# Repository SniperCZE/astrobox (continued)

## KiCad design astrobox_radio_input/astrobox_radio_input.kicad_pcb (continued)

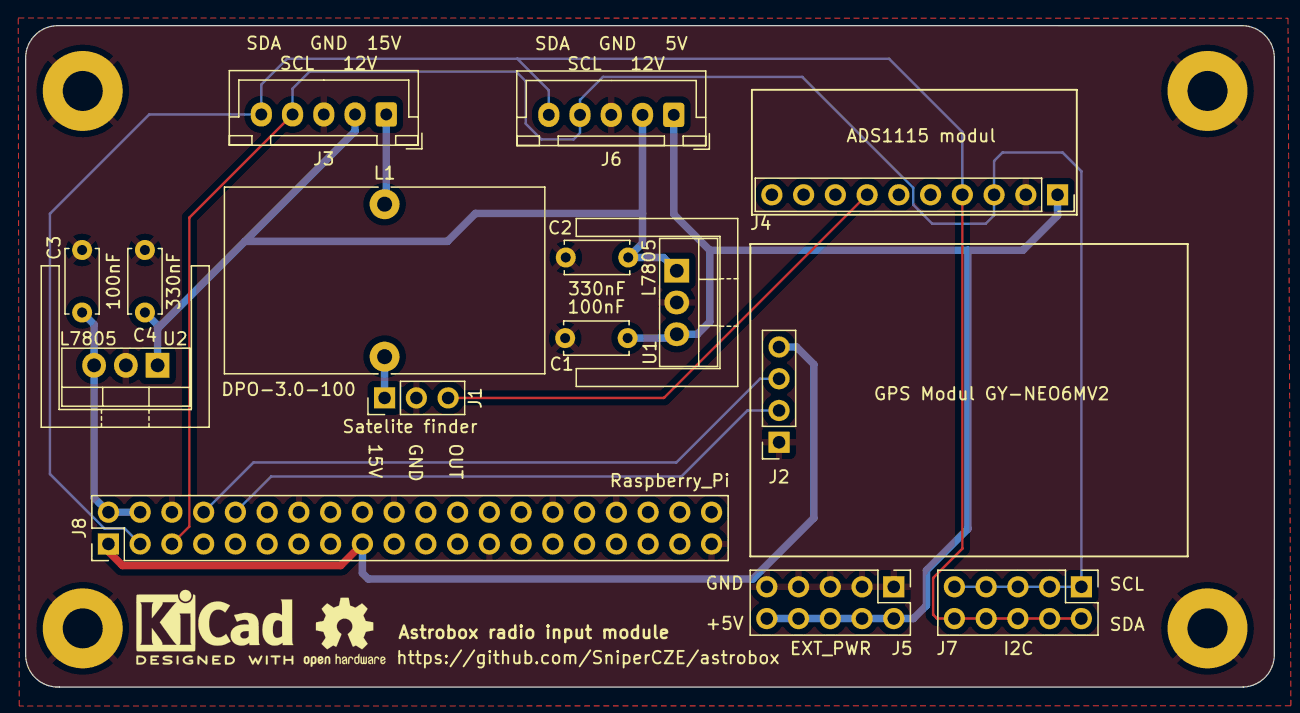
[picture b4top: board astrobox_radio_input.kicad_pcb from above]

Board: 2 copper layers, 99.9 x 52.9 mm, 15 parts (0 on the bottom side), 12 nets.

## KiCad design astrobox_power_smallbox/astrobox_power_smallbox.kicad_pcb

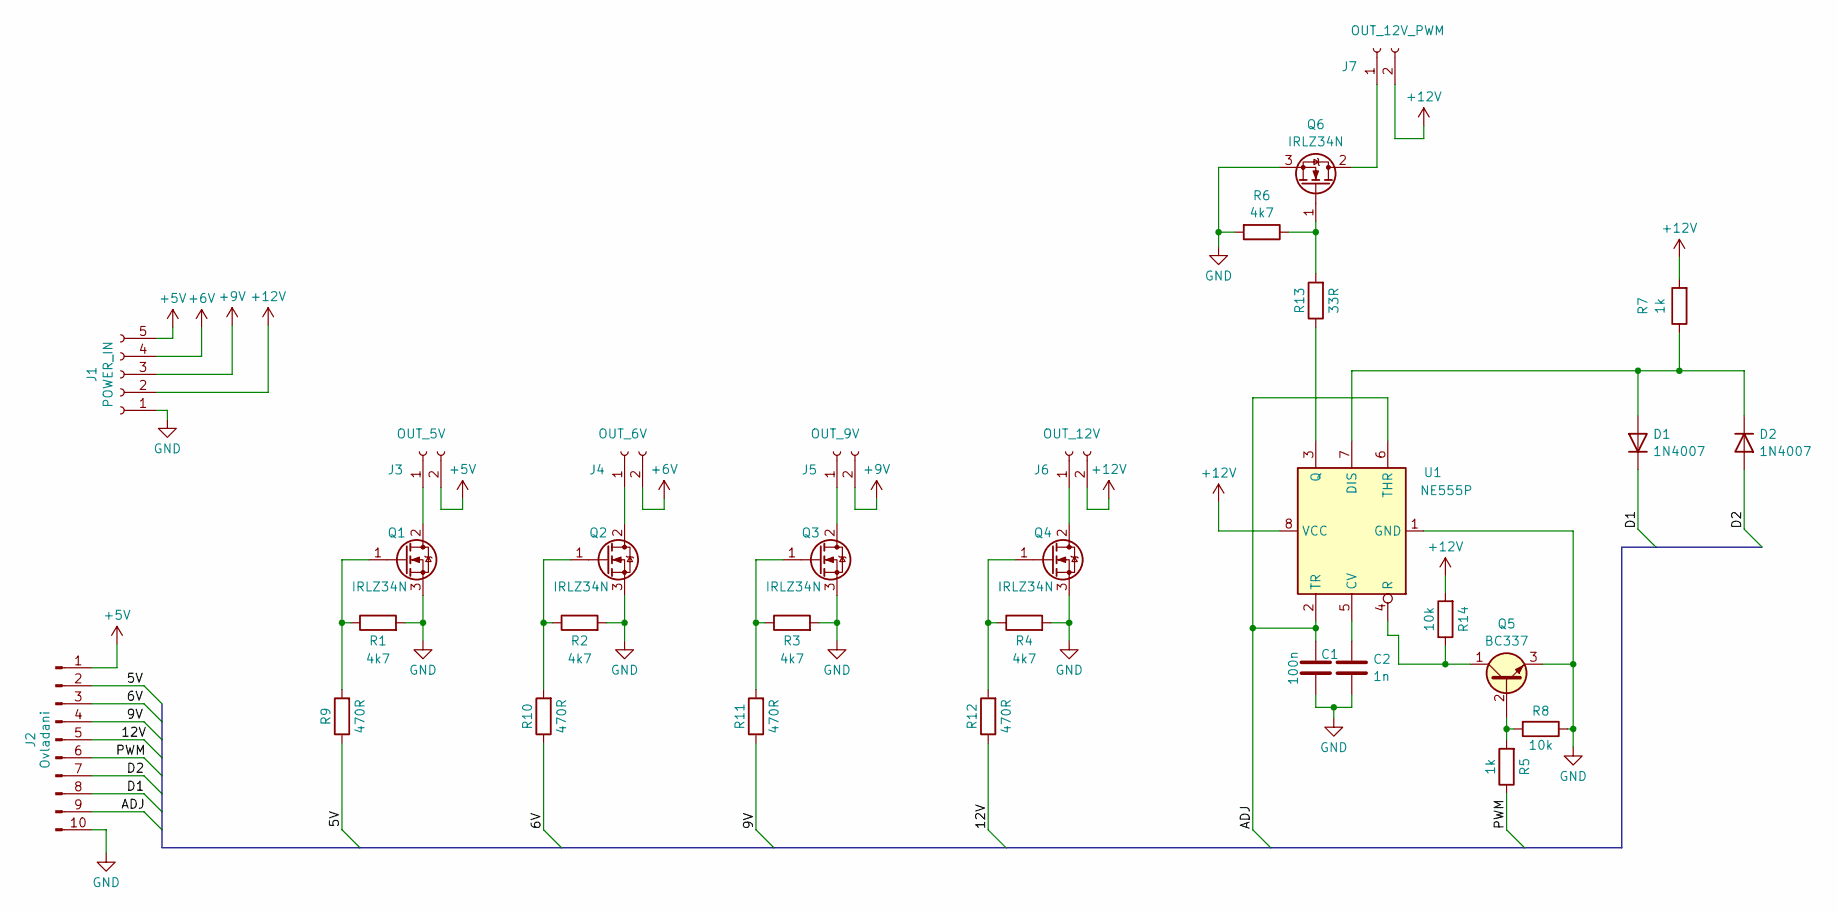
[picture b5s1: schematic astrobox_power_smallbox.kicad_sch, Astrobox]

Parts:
C1: 100n; C_Disc_D9.0mm_W5.0mm_P5.00mm
C2: 1n; C_Disc_D9.0mm_W5.0mm_P5.00mm
D1, D2: 1N4007; D_DO-15_P12.70mm_Horizontal
J1: POWER_IN; SolderWire-1sqmm_1x05_P5.4mm_D1.4mm_OD2.7mm
J2: Ovladani; PinHeader_1x10_P2.54mm_Vertical
J3: OUT_5V; SolderWire-1.5sqmm_1x02_P6mm_D1.7mm_OD3mm
J4: OUT_6V; SolderWire-1.5sqmm_1x02_P6mm_D1.7mm_OD3mm
J5: OUT_9V; SolderWire-1.5sqmm_1x02_P6mm_D1.7mm_OD3mm
J6: OUT_12V; SolderWire-1.5sqmm_1x02_P6mm_D1.7mm_OD3mm
J7: OUT_12V_PWM; SolderWire-1.5sqmm_1x02_P6mm_D1.7mm_OD3mm
Q1, Q2, Q3, Q4, Q6: IRLZ34N; TO-220-3_Vertical
Q5: BC337; TO-92_HandSolder
R1, R2, R3, R4, R6: 4k7; R_Axial_DIN0309_L9.0mm_D3.2mm_P12.70mm_Horizontal
R5, R7: 1k; R_Axial_DIN0309_L9.0mm_D3.2mm_P12.70mm_Horizontal
R8, R14: 10k; R_Axial_DIN0309_L9.0mm_D3.2mm_P12.70mm_Horizontal
R9, R10, R11, R12: 470R; R_Axial_DIN0309_L9.0mm_D3.2mm_P12.70mm_Horizontal
R13: 33R; R_Axial_DIN0309_L9.0mm_D3.2mm_P12.70mm_Horizontal
U1: NE555P; DIP-8_W7.62mm

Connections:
+5V: J1.5, J2.1, J3.2
+6V: J1.4, J4.2
+9V: J1.3, J5.2
+12V: J1.2, J6.2, J7.2, R7.2, R14.2, U1.8 (VCC)
/5V: J2.2, R9.1
/6V: J2.3, R10.1
/9V: J2.4, R11.1
/12V: J2.5, R12.1
/ADJ: C1.1, J2.9, U1.2 (TR), U1.6 (THR)
/D1: D1.1 (K), J2.8
/D2: D2.2 (A), J2.7
/PWM: J2.6, R5.1
GND: C1.2, C2.2, J1.1, J2.10, Q1.3 (S), Q2.3 (S), Q3.3 (S), Q4.3 (S), Q5.3 (E), Q6.3 (S), R1.2, R2.2, R3.2, R4.2, R6.2, R8.1, U1.1 (GND)
unnamed: D1.2 (A), D2.1 (K), R7.1, U1.7 (DIS)
unnamed: J3.1, Q1.2 (D)
unnamed: J4.1, Q2.2 (D)
unnamed: J5.1, Q3.2 (D)
unnamed: J6.1, Q4.2 (D)
unnamed: J7.1, Q6.2 (D)
unnamed: Q1.1 (G), R1.1, R9.2
unnamed: Q2.1 (G), R2.1, R10.2
unnamed: Q3.1 (G), R3.1, R11.2
unnamed: Q4.1 (G), R4.1, R12.2
unnamed: Q5.2 (B), R5.2, R8.2
unnamed: Q5.1 (C), R14.1, U1.4 (R)
unnamed: Q6.1 (G), R6.1, R13.2
unnamed: C2.1, U1.5 (CV)
unnamed: R13.1, U1.3 (Q)

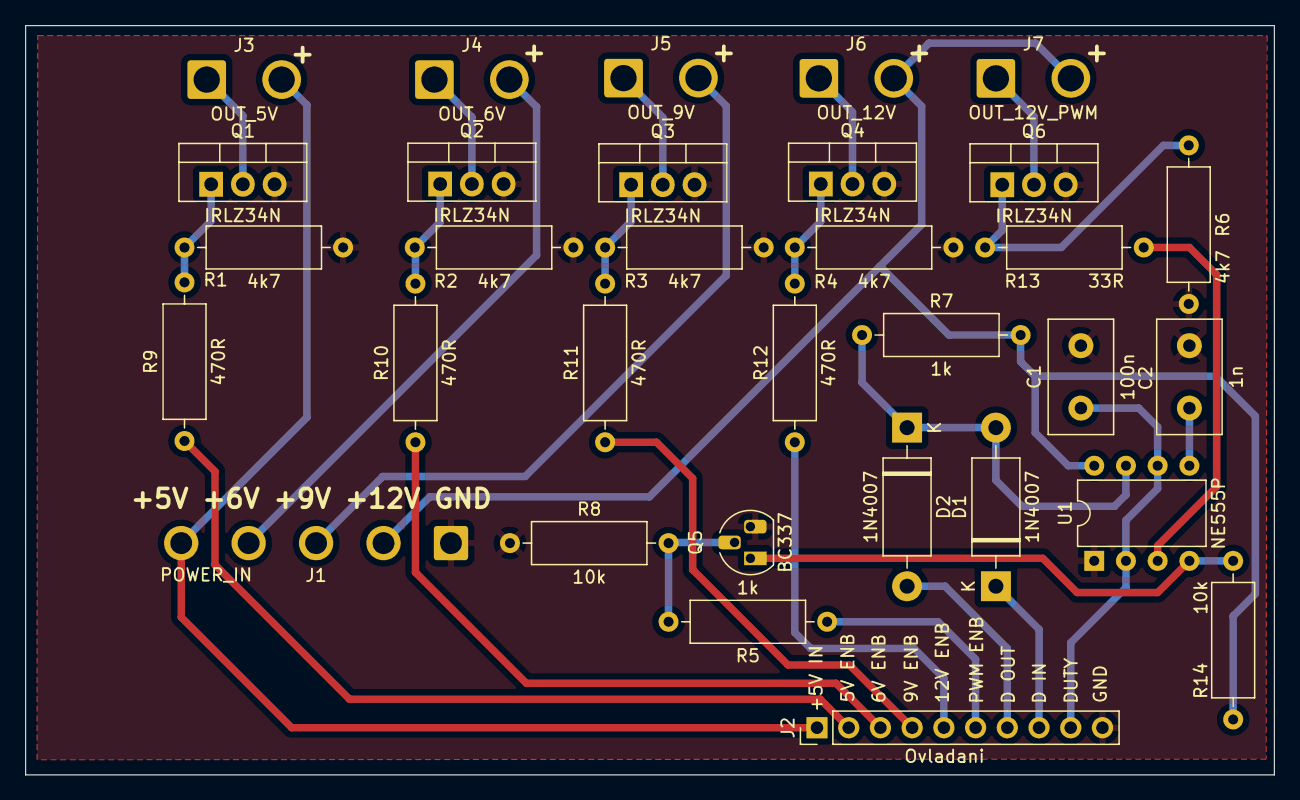
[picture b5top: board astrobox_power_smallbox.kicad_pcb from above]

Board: 2 copper layers, 100.0 x 60.0 mm, 32 parts (0 on the bottom side), 28 nets.

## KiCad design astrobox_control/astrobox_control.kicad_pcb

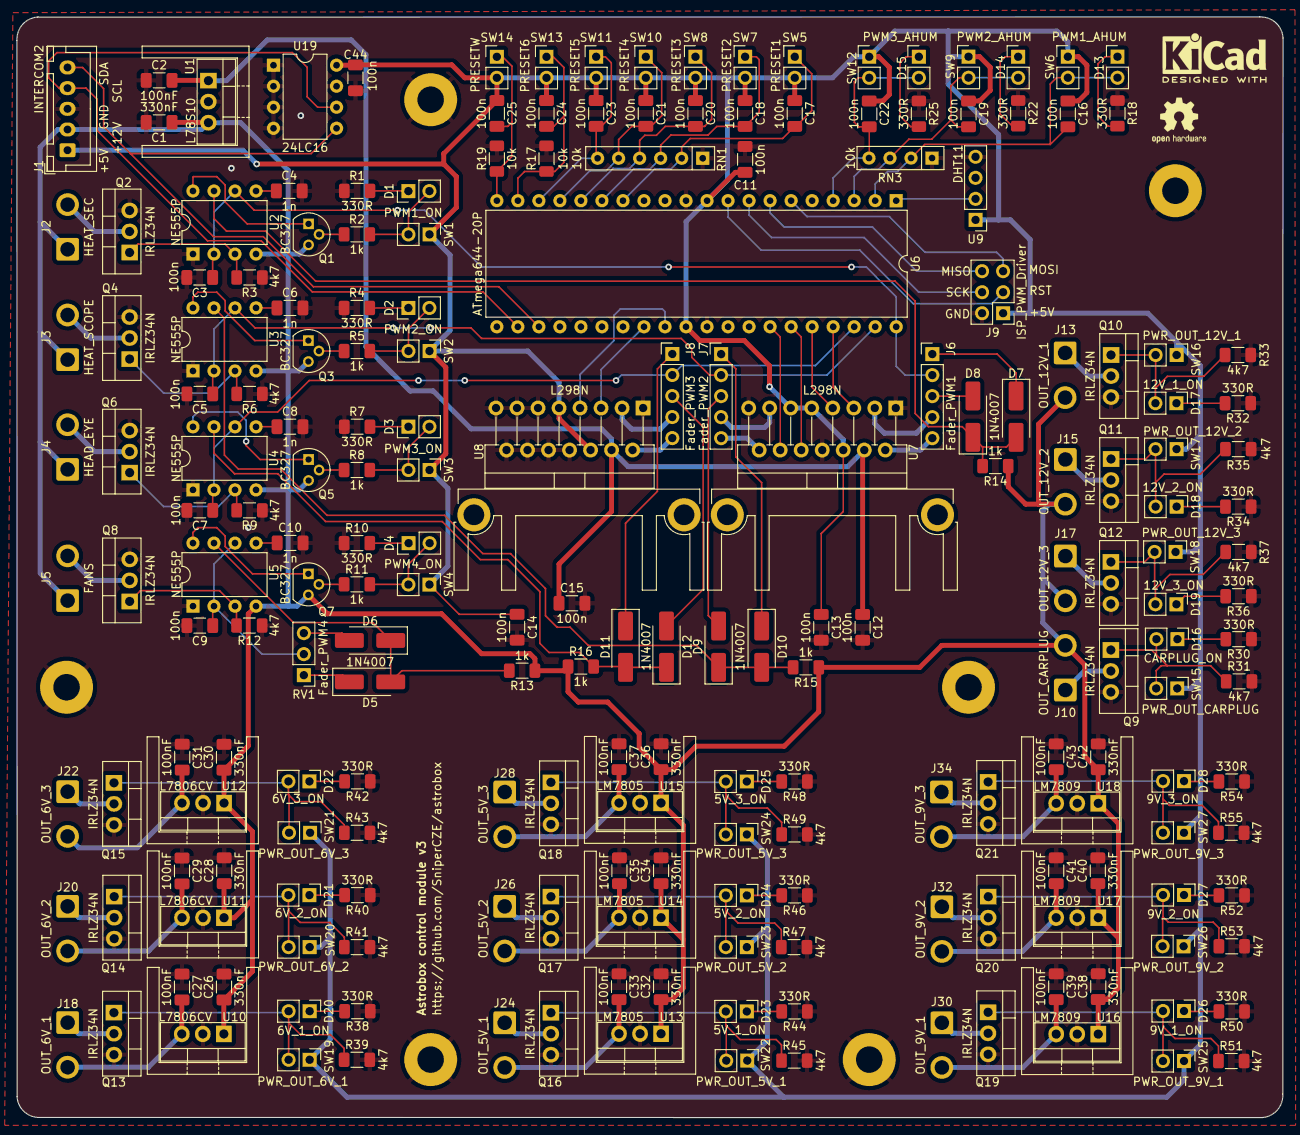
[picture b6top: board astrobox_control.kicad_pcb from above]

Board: 2 copper layers, 153.0 x 133.0 mm, 211 parts (0 on the bottom side), 128 nets.

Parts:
C1, C26, C28, C30, C32, C34, C36, C38, C40, C42: 330nF; C_1206_3216Metric_Pad1.33x1.80mm_HandSolder
C2, C27, C29, C31, C33, C35, C37, C39, C41, C43: 100nF; C_1206_3216Metric_Pad1.33x1.80mm_HandSolder
C3, C5, C7, C9, C11, C12, C13, C14, C15, C16, C17, C18, C19, C20, C21, C22, C23, C24, C25, C44: 100n; C_1206_3216Metric_Pad1.33x1.80mm_HandSolder
C4, C6, C8, C10: 1n; C_1206_3216Metric_Pad1.33x1.80mm_HandSolder
D1: PWM1_ON; PinHeader_1x02_P2.54mm_Vertical
D2: PWM2_ON; PinHeader_1x02_P2.54mm_Vertical
D3: PWM3_ON; PinHeader_1x02_P2.54mm_Vertical
D4: PWM4_ON; PinHeader_1x02_P2.54mm_Vertical
D5, D6, D7, D8, D9, D10, D11, D12: 1N4007; D_SMA_Handsoldering
D13: PWM1_AHUM; PinHeader_1x02_P2.54mm_Vertical
D14: PWM2_AHUM; PinHeader_1x02_P2.54mm_Vertical
D15: PWM3_AHUM; PinHeader_1x02_P2.54mm_Vertical
D16: CARPLUG_ON; PinHeader_1x02_P2.54mm_Vertical
D17: 12V_1_ON; PinHeader_1x02_P2.54mm_Vertical
D18: 12V_2_ON; PinHeader_1x02_P2.54mm_Vertical
D19: 12V_3_ON; PinHeader_1x02_P2.54mm_Vertical
D20: 6V_1_ON; PinHeader_1x02_P2.54mm_Vertical
D21: 6V_2_ON; PinHeader_1x02_P2.54mm_Vertical
D22: 6V_3_ON; PinHeader_1x02_P2.54mm_Vertical
D23: 5V_1_ON; PinHeader_1x02_P2.54mm_Vertical
D24: 5V_2_ON; PinHeader_1x02_P2.54mm_Vertical
D25: 5V_3_ON; PinHeader_1x02_P2.54mm_Vertical
D26: 9V_1_ON; PinHeader_1x02_P2.54mm_Vertical
D27: 9V_2_ON; PinHeader_1x02_P2.54mm_Vertical
D28: 9V_3_ON; PinHeader_1x02_P2.54mm_Vertical
J1: INTERCOM2; JST_XH_B5B-XH-A_1x05_P2.50mm_Vertical
J2: HEAT_SEC; SolderWire-1sqmm_1x02_P5.4mm_D1.4mm_OD2.7mm
J3: HEAT_SCOPE; SolderWire-1sqmm_1x02_P5.4mm_D1.4mm_OD2.7mm
J4: HEAD_EYE; SolderWire-1sqmm_1x02_P5.4mm_D1.4mm_OD2.7mm
J5: FANS; SolderWire-1sqmm_1x02_P5.4mm_D1.4mm_OD2.7mm
J6: Fader_PWM1; PinHeader_1x05_P2.54mm_Vertical
J7: Fader_PWM2; PinHeader_1x05_P2.54mm_Vertical
J8: Fader_PWM3; PinHeader_1x05_P2.54mm_Vertical
J9: ISP_PWM_Driver; PinHeader_2x03_P2.54mm_Vertical
J10: OUT_CARPLUG; SolderWire-1sqmm_1x02_P5.4mm_D1.4mm_OD2.7mm
J13: OUT_12V_1; SolderWire-1sqmm_1x02_P5.4mm_D1.4mm_OD2.7mm
J15: OUT_12V_2; SolderWire-1sqmm_1x02_P5.4mm_D1.4mm_OD2.7mm
J17: OUT_12V_3; SolderWire-1sqmm_1x02_P5.4mm_D1.4mm_OD2.7mm
J18: OUT_6V_1; SolderWire-1sqmm_1x02_P5.4mm_D1.4mm_OD2.7mm
J20: OUT_6V_2; SolderWire-1sqmm_1x02_P5.4mm_D1.4mm_OD2.7mm
J22: OUT_6V_3; SolderWire-1sqmm_1x02_P5.4mm_D1.4mm_OD2.7mm
J24: OUT_5V_1; SolderWire-1sqmm_1x02_P5.4mm_D1.4mm_OD2.7mm
J26: OUT_5V_2; SolderWire-1sqmm_1x02_P5.4mm_D1.4mm_OD2.7mm
J28: OUT_5V_3; SolderWire-1sqmm_1x02_P5.4mm_D1.4mm_OD2.7mm
J30: OUT_9V_1; SolderWire-1sqmm_1x02_P5.4mm_D1.4mm_OD2.7mm
J32: OUT_9V_2; SolderWire-1sqmm_1x02_P5.4mm_D1.4mm_OD2.7mm
J34: OUT_9V_3; SolderWire-1sqmm_1x02_P5.4mm_D1.4mm_OD2.7mm
Q1, Q3, Q5, Q7: BC327; TO-92
Q2, Q4, Q6, Q8, Q9, Q10, Q11, Q12, Q13, Q14, Q15, Q16, Q17, Q18, Q19, Q20, Q21: IRLZ34N; TO-220-3_Vertical
R1, R4, R7, R10, R18, R22, R25, R30, R32, R34, R36, R38, R40, R42, R44, R46, R48, R50, R52, R54: 330R; R_1206_3216Metric_Pad1.30x1.75mm_HandSolder
R2, R5, R8, R11, R13, R14, R15, R16: 1k; R_1206_3216Metric_Pad1.30x1.75mm_HandSolder
R3, R6, R9, R12, R31, R33, R35, R37, R39, R41, R43, R45, R47, R49, R51, R53, R55: 4k7; R_1206_3216Metric_Pad1.30x1.75mm_HandSolder
R17, R19: 10k; R_1206_3216Metric_Pad1.30x1.75mm_HandSolder
RN1: 10k; R_Array_SIP6
RN3: 10k; R_Array_SIP4
RV1: Fader_PWM4; PinHeader_1x03_P2.54mm_Vertical
SW1: PWM1_ON; PinHeader_1x02_P2.54mm_Vertical
SW2: PWM2_ON; PinHeader_1x02_P2.54mm_Vertical
SW3: PWM3_ON; PinHeader_1x02_P2.54mm_Vertical
SW4: PWM4_ON; PinHeader_1x02_P2.54mm_Vertical
SW5: PRESET1; PinHeader_1x02_P2.54mm_Vertical
SW6: PWM1_AUTOHUM; PinHeader_1x02_P2.54mm_Vertical
SW7: PRESET2; PinHeader_1x02_P2.54mm_Vertical
SW8: PRESET3; PinHeader_1x02_P2.54mm_Vertical
SW9: PWM2_AUTOHUM; PinHeader_1x02_P2.54mm_Vertical
SW10: PRESET4; PinHeader_1x02_P2.54mm_Vertical
SW11: PRESET5; PinHeader_1x02_P2.54mm_Vertical
SW12: PWM3_AUTOHUM; PinHeader_1x02_P2.54mm_Vertical
SW13: PRESET6; PinHeader_1x02_P2.54mm_Vertical
SW14: PRESETW; PinHeader_1x02_P2.54mm_Vertical
SW15: PWR_OUT_CARPLUG; PinHeader_1x02_P2.54mm_Vertical
SW16: PWR_OUT_12V_1; PinHeader_1x02_P2.54mm_Vertical
SW17: PWR_OUT_12V_2; PinHeader_1x02_P2.54mm_Vertical
SW18: PWR_OUT_12V_3; PinHeader_1x02_P2.54mm_Vertical
SW19: PWR_OUT_6V_1; PinHeader_1x02_P2.54mm_Vertical
SW20: PWR_OUT_6V_2; PinHeader_1x02_P2.54mm_Vertical
SW21: PWR_OUT_6V_3; PinHeader_1x02_P2.54mm_Vertical
SW22: PWR_OUT_5V_1; PinHeader_1x02_P2.54mm_Vertical
SW23: PWR_OUT_5V_2; PinHeader_1x02_P2.54mm_Vertical
SW24: PWR_OUT_5V_3; PinHeader_1x02_P2.54mm_Vertical
SW25: PWR_OUT_9V_1; PinHeader_1x02_P2.54mm_Vertical
SW26: PWR_OUT_9V_2; PinHeader_1x02_P2.54mm_Vertical
SW27: PWR_OUT_9V_3; PinHeader_1x02_P2.54mm_Vertical
U1: L78S10; TO-220-3_Vertical
U2, U3, U4, U5: NE555P; DIP-8_W7.62mm
U6: ATmega644-20P; DIP-40_W15.24mm
U7, U8: L298N; TO-220-15_P2.54x2.54mm_StaggerOdd_Lead4.58mm_Vertical
U9: DHT11; PinHeader_1x04_P2.54mm_Vertical
U10, U11, U12: L7806CV; TO-220-3_Vertical
U13, U14, U15: LM7805; TO-220-3_Vertical
U16, U17, U18: LM7809; TO-220-3_Vertical
U19: 24LC16; DIP-8_W7.62mm

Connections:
+5V: C11.1, C13.1, C14.1, C16.1, C17.1, C18.1, C19.1, C20.1, C21.1, C22.1, C23.1, C24.1, C25.1, C44.1, J1.1, J9.1, SW1.1 (A), SW2.1 (A), SW3.1 (A), SW4.1 (A), SW5.2, SW6.1 (A), SW7.2, SW8.2, SW9.1 (A), SW10.2, SW11.2, SW12.1 (A), SW13.2, SW14.2, SW15.1 (A), SW16.1 (A), SW17.1 (A), SW18.1 (A), SW19.1 (A), SW20.1 (A), SW21.1 (A), SW22.1 (A), SW23.1 (A), SW24.1 (A), SW25.1 (A), SW26.1 (A), SW27.1 (A), U6.10 (VCC), U6.30 (AVCC), U7.6 (EnA), U7.9 (Vss), U7.11 (EnB), U8.6 (EnA), U8.9 (Vss), U9.1 (VDD), U19.8 (VCC)
+10V: C2.2, C12.1, C15.1, U1.1 (VO), U7.4 (Vs), U8.4 (Vs)
+12V: C1.1, C26.1, C28.1, C30.1, C32.1, C34.1, C36.1, C38.1, C40.1, C42.1, J1.2, J2.1, J3.1, J4.1, J5.1, J10.2, J13.2, J15.2, J17.2, Q1.3 (E), Q3.3 (E), Q5.3 (E), Q7.3 (E), R13.1, R14.1, R15.1, R16.1, U1.3 (VI), U2.4 (R), U3.4 (R), U4.4 (R), U5.4 (R), U10.1 (VI), U11.1 (VI), U12.1 (VI), U13.1 (VI), U14.1 (VI), U15.1 (VI), U16.1 (VI), U17.1 (VI), U18.1 (VI)
/PWM control plane/AUTOHUM1: C16.2, D13.2 (A), RN3.2 (R1.2), SW6.2 (B), U6.2 (PB1)
/PWM control plane/AUTOHUM2: C19.2, D14.2 (A), RN3.3 (R2.2), SW9.2 (B), U6.3 (PB2)
/PWM control plane/AUTOHUM3: C22.2, D15.2 (A), RN3.4 (R3.2), SW12.2 (B), U6.4 (PB3)
/PWM control plane/DHT11: U6.1 (PB0), U9.2 (DATA)
/PWM control plane/FADER1: C3.1, J6.2, U2.2 (TR), U2.6 (THR), U6.40 (PA0)
/PWM control plane/FADER2: C5.1, J7.2, U3.2 (TR), U3.6 (THR), U6.39 (PA1)
/PWM control plane/FADER3: C7.1, J8.2, U4.2 (TR), U4.6 (THR), U6.38 (PA2)
/PWM control plane/MISO: J9.6, U6.7 (PB6)
/PWM control plane/MOSI: J9.5, U6.6 (PB5)
/PWM control plane/PRESET1: C17.2, RN1.2 (R1.2), SW5.1, U6.14 (PD0)
/PWM control plane/PRESET2: C18.2, RN1.3 (R2.2), SW7.1, U6.15 (PD1)
/PWM control plane/PRESET3: C20.2, RN1.4 (R3.2), SW8.1, U6.16 (PD2)
/PWM control plane/PRESET4: C21.2, RN1.5 (R4.2), SW10.1, U6.17 (PD3)
/PWM control plane/PRESET5: C23.2, RN1.6 (R5.2), SW11.1, U6.18 (PD4)
/PWM control plane/PRESET6: C24.2, R17.1, SW13.1, U6.19 (PD5)
/PWM control plane/PRESETW: C25.2, R19.1, SW14.1, U6.20 (PD6)
/PWM control plane/PWM_1 555-7 OUT: D7.2 (A), D8.1 (K), R14.2, U2.7 (DIS)
/PWM control plane/PWM_2 555-7 OUT: D9.1 (K), D10.2 (A), R15.2, U3.7 (DIS)
/PWM control plane/PWM_3 555-7 OUT: D11.2 (A), D12.1 (K), R16.2, U4.7 (DIS)
/PWM control plane/PWM_4 555-7 OUT: D5.2 (A), D6.1 (K), R13.2, U5.7 (DIS)
/PWM control plane/PWM_4 OUT: C9.1, RV1.2, U5.2 (TR), U5.6 (THR)
/PWM control plane/RST: J9.3, U6.9 (~RESET)
/PWM control plane/SCK: J9.4, U6.8 (PB7)
/PWM control plane/SCL: J1.4, U6.22 (PC0), U19.6 (SCL)
/PWM control plane/SDA: J1.5, U6.23 (PC1), U19.5 (SDA)
GND: C1.2, C2.1, C3.2, C4.2, C5.2, C6.2, C7.2, C8.2, C9.2, C10.2, C11.2, C12.2, C13.2, C14.2, C15.2, C26.2, C27.1, C28.2, C29.1, C30.2, C31.1, C32.2, C33.1, C34.2, C35.1, C36.2, C37.1, C38.2, C39.1, C40.2, C41.1, C42.2, C43.1, C44.2, J1.3, J9.2, Q2.3 (S), Q4.3 (S), Q6.3 (S), Q8.3 (S), Q9.3 (S), Q10.3 (S), Q11.3 (S), Q12.3 (S), Q13.3 (S), Q14.3 (S), Q15.3 (S), Q16.3 (S), Q17.3 (S), Q18.3 (S), Q19.3 (S), Q20.3 (S), Q21.3 (S), R1.1, R3.1, R4.1, R6.1, R7.1, R9.1, R10.1, R12.1, R17.2, R18.1, R19.2, R22.1, R25.1, R30.1, R31.2, R32.1, R33.2, R34.1, R35.2, R36.1, R37.2, R38.1, R39.2, R40.1, R41.2, R42.1, R43.2, R44.1, R45.2, R46.1, R47.2, R48.1, R49.2, R50.1, R51.2, R52.1, R53.2, R54.1, R55.2, RN1.1 (R1), RN3.1 (R1), U1.2 (GND), U2.1 (GND), U3.1 (GND), U4.1 (GND), U5.1 (GND), U6.11 (GND), U6.31 (GND), U7.1 (SENSE_A), U7.8 (GND), U7.15 (SENSE_B), U8.1 (SENSE_A), U8.8 (GND), U8.10 (IN3), U8.11 (EnB), U8.12 (IN4), U8.13 (OUT3), U8.14 (OUT4), U8.15 (SENSE_B), U9.4 (GND), U10.2 (GND), U11.2 (GND), U12.2 (GND), U13.2 (GND), U14.2 (GND), U15.2 (GND), U16.2 (GND), U17.2 (GND), U18.2 (GND), U19.1 (A0), U19.2 (A1), U19.3 (A2), U19.4 (GND), U19.7 (WP)
unnamed: D1.2 (A), R2.2, SW1.2 (B)
unnamed: D1.1 (K), R1.2
unnamed: D2.2 (A), R5.2, SW2.2 (B)
unnamed: D2.1 (K), R4.2
unnamed: D3.2 (A), R8.2, SW3.2 (B)
unnamed: D3.1 (K), R7.2
unnamed: D4.2 (A), R11.2, SW4.2 (B)
unnamed: D4.1 (K), R10.2
unnamed: D5.1 (K), RV1.1
unnamed: D6.2 (A), RV1.3
unnamed: D7.1 (K), J6.1
unnamed: D8.2 (A), J6.3
unnamed: D9.2 (A), J7.3
unnamed: D10.1 (K), J7.1
unnamed: D11.1 (K), J8.1
unnamed: D12.2 (A), J8.3
unnamed: D13.1 (K), R18.2
unnamed: D14.1 (K), R22.2
unnamed: D15.1 (K), R25.2
unnamed: D16.2 (A), Q9.1 (G), R31.1, SW15.2 (B)
unnamed: D16.1 (K), R30.2
unnamed: D17.2 (A), Q10.1 (G), R33.1, SW16.2 (B)
unnamed: D17.1 (K), R32.2
unnamed: D18.2 (A), Q11.1 (G), R35.1, SW17.2 (B)
unnamed: D18.1 (K), R34.2
unnamed: D19.2 (A), Q12.1 (G), R37.1, SW18.2 (B)
unnamed: D19.1 (K), R36.2
unnamed: D20.2 (A), Q13.1 (G), R39.1, SW19.2 (B)
unnamed: D20.1 (K), R38.2
unnamed: D21.2 (A), Q14.1 (G), R41.1, SW20.2 (B)
unnamed: D21.1 (K), R40.2
unnamed: D22.2 (A), Q15.1 (G), R43.1, SW21.2 (B)
unnamed: D22.1 (K), R42.2
unnamed: D23.2 (A), Q16.1 (G), R45.1, SW22.2 (B)
unnamed: D23.1 (K), R44.2
unnamed: D24.2 (A), Q17.1 (G), R47.1, SW23.2 (B)
unnamed: D24.1 (K), R46.2
unnamed: D25.2 (A), Q18.1 (G), R49.1, SW24.2 (B)
unnamed: D25.1 (K), R48.2
unnamed: D26.2 (A), Q19.1 (G), R51.1, SW25.2 (B)
unnamed: D26.1 (K), R50.2
unnamed: D27.2 (A), Q20.1 (G), R53.1, SW26.2 (B)
unnamed: D27.1 (K), R52.2
unnamed: D28.2 (A), Q21.1 (G), R55.1, SW27.2 (B)
unnamed: D28.1 (K), R54.2
unnamed: J2.2, Q2.2 (D)
unnamed: J3.2, Q4.2 (D)
unnamed: J4.2, Q6.2 (D)
unnamed: J5.2, Q8.2 (D)
unnamed: J6.4, U7.3 (OUT2)
unnamed: J6.5, U7.2 (OUT1)
unnamed: J7.4, U7.13 (OUT3)
unnamed: J7.5, U7.14 (OUT4)
unnamed: J8.4, U8.3 (OUT2)
unnamed: J8.5, U8.2 (OUT1)
unnamed: J10.1, Q9.2 (D)
unnamed: J13.1, Q10.2 (D)
unnamed: J15.1, Q11.2 (D)
unnamed: J17.1, Q12.2 (D)
unnamed: J18.1, Q13.2 (D)
unnamed: C27.2, J18.2, U10.3 (VO)
unnamed: J20.1, Q14.2 (D)
unnamed: C29.2, J20.2, U11.3 (VO)
unnamed: J22.1, Q15.2 (D)
unnamed: C31.2, J22.2, U12.3 (VO)
unnamed: J24.1, Q16.2 (D)
unnamed: C33.2, J24.2, U13.3 (VO)
unnamed: J26.1, Q17.2 (D)
unnamed: C35.2, J26.2, U14.3 (VO)
unnamed: J28.1, Q18.2 (D)
unnamed: C37.2, J28.2, U15.3 (VO)
unnamed: J30.1, Q19.2 (D)
unnamed: C39.2, J30.2, U16.3 (VO)
unnamed: J32.1, Q20.2 (D)
unnamed: C41.2, J32.2, U17.3 (VO)
unnamed: J34.1, Q21.2 (D)
unnamed: C43.2, J34.2, U18.3 (VO)
unnamed: Q1.2 (B), R2.1
unnamed: Q1.1 (C), U2.8 (VCC)
unnamed: Q2.1 (G), R3.2, U2.3 (Q)
unnamed: Q3.2 (B), R5.1
unnamed: Q3.1 (C), U3.8 (VCC)
unnamed: Q4.1 (G), R6.2, U3.3 (Q)
unnamed: Q5.2 (B), R8.1
unnamed: Q5.1 (C), U4.8 (VCC)
unnamed: Q6.1 (G), R9.2, U4.3 (Q)
unnamed: Q7.2 (B), R11.1
unnamed: Q7.1 (C), U5.8 (VCC)
unnamed: Q8.1 (G), R12.2, U5.3 (Q)
unnamed: C4.1, U2.5 (CV)
unnamed: C6.1, U3.5 (CV)
unnamed: C8.1, U4.5 (CV)
unnamed: C10.1, U5.5 (CV)
unnamed: U6.37 (PA3), U7.5 (IN1)
unnamed: U6.36 (PA4), U7.7 (IN2)
unnamed: U6.35 (PA5), U7.10 (IN3)
unnamed: U6.34 (PA6), U7.12 (IN4)
unnamed: U6.28 (PC6), U8.5 (IN1)
unnamed: U6.29 (PC7), U8.7 (IN2)

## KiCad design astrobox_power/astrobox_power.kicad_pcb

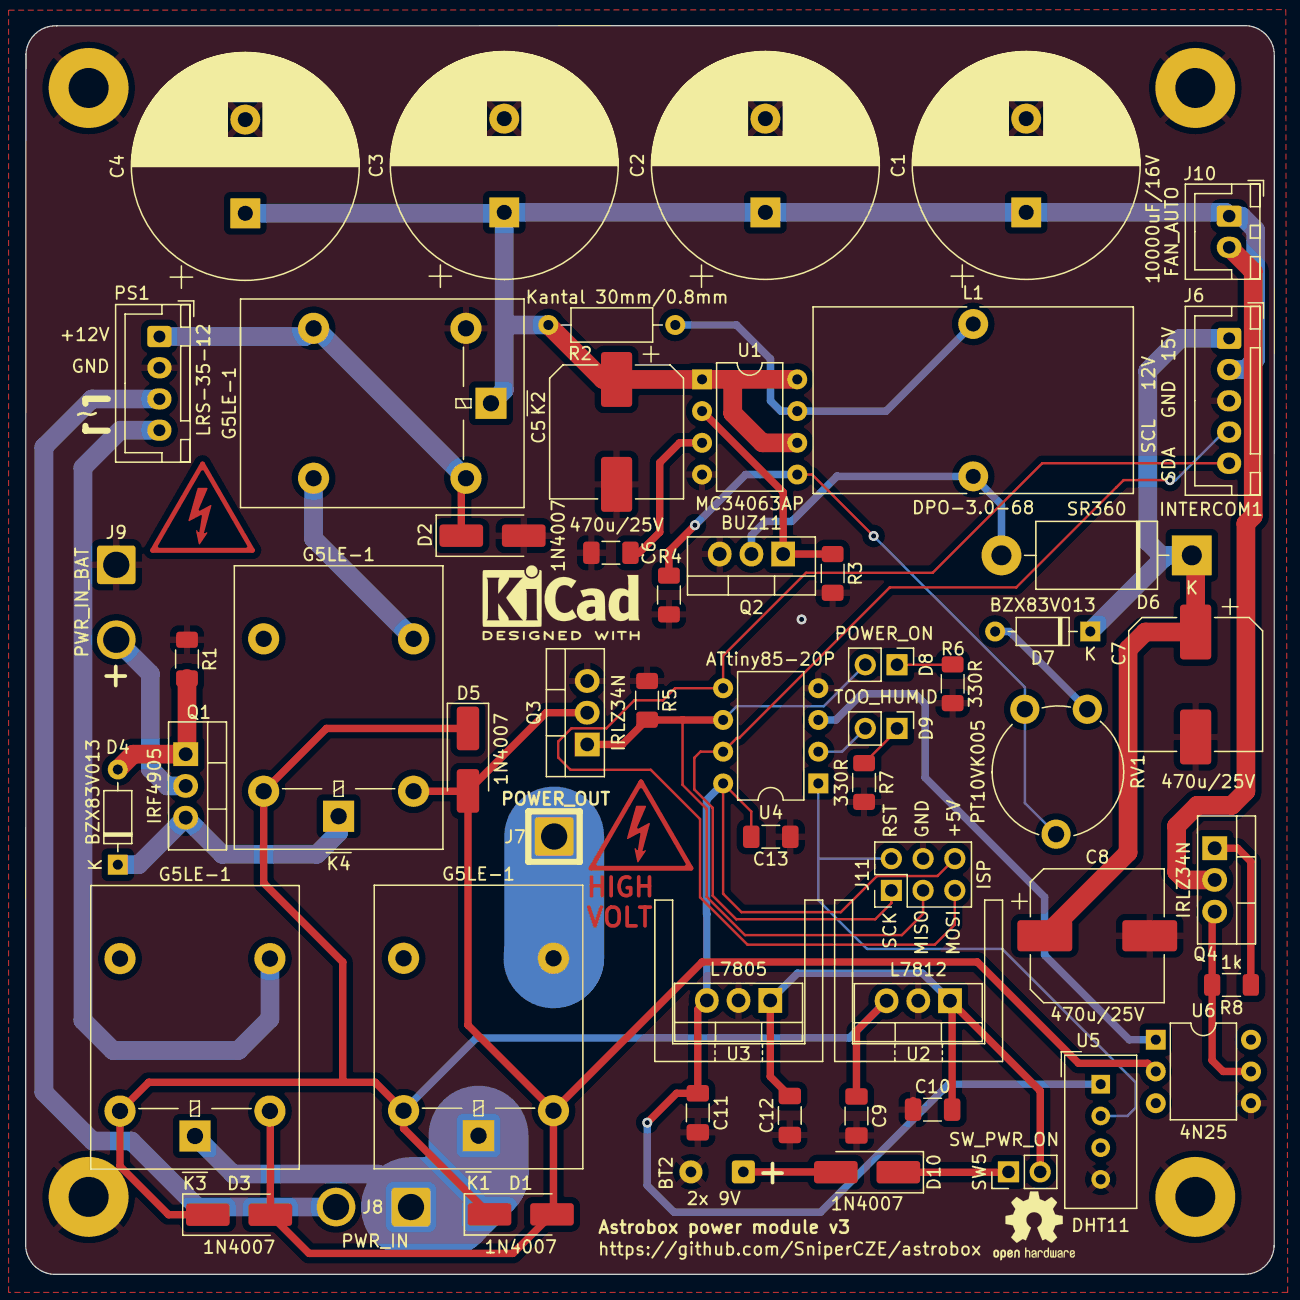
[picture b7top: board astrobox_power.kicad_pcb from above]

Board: 2 copper layers, 100.0 x 100.0 mm, 56 parts (0 on the bottom side), 35 nets.

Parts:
BT2: 2x 9V; SolderWire-0.25sqmm_1x02_P4.2mm_D0.65mm_OD1.7mm
C1, C2, C3, C4: 10000uF/16V; CP_Radial_D18.0mm_P7.50mm
C5, C7, C8: 470u/25V; CP_Elec_10x10.5
C6: 220p; C_1206_3216Metric_Pad1.33x1.80mm_HandSolder
C9, C11, C13: 100nF; C_1206_3216Metric_Pad1.33x1.80mm_HandSolder
C10, C12: 330nF; C_1206_3216Metric_Pad1.33x1.80mm_HandSolder
D1, D2, D3, D5, D10: 1N4007; D_SMA_Handsoldering
D4, D7: BZX83V013; D_DO-35_SOD27_P7.62mm_Horizontal
D6: SR360; D_DO-201AD_P15.24mm_Horizontal
D8: POWER_ON; PinHeader_1x02_P2.54mm_Vertical
D9: TOO_HUMID; PinHeader_1x02_P2.54mm_Vertical
J6: INTERCOM1; JST_XH_B5B-XH-A_1x05_P2.50mm_Vertical
J7: POWER_OUT; SolderWire-1.5sqmm_1x01_D1.7mm_OD3mm
J8: PWR_IN; SolderWire-1.5sqmm_1x02_P6mm_D1.7mm_OD3mm
J9: PWR_IN_BAT; SolderWire-1.5sqmm_1x02_P6mm_D1.7mm_OD3mm
J10: FAN_AUTO; JST_XH_B2B-XH-A_1x02_P2.50mm_Vertical
J11: ISP; PinHeader_2x03_P2.54mm_Vertical
K1, K2, K3, K4: G5LE-1; Relay_SPDT_Omron-G5LE-1
L1: DPO-3.0-68; L_Toroid_Vertical_L25.4mm_W14.7mm_P12.20mm_Vishay_TJ5
PS1: LRS-35-12; JST_XH_B4B-XH-A_1x04_P2.50mm_Vertical
Q1: IRF4905; TO-220-3_Vertical
Q2: BUZ11; TO-220-3_Vertical
Q3, Q4: IRLZ34N; TO-220-3_Vertical
R1, R5: 4k7; R_1206_3216Metric_Pad1.30x1.75mm_HandSolder
R2: Kantal 30mm/0.8mm; R_Axial_DIN0207_L6.3mm_D2.5mm_P10.16mm_Horizontal
R3: 560R; R_1206_3216Metric_Pad1.30x1.75mm_HandSolder
R4: 2k; R_1206_3216Metric_Pad1.30x1.75mm_HandSolder
R6, R7: 330R; R_1206_3216Metric_Pad1.30x1.75mm_HandSolder
R8: 1k; R_1206_3216Metric_Pad1.30x1.75mm_HandSolder
RV1: PT10VK005; Potentiometer_Piher_PT-10-V10_Vertical
SW5: SW_PWR_ON; PinHeader_1x02_P2.54mm_Vertical
U1: MC34063AP; DIP-8_W7.62mm
U2: L7812; TO-220-3_Vertical
U3: L7805; TO-220-3_Vertical
U4: ATtiny85-20P; DIP-8_W7.62mm
U5: DHT11; Aosong_DHT11_5.5x12.0_P2.54mm
U6: 4N25; DIP-6_W7.62mm

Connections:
+12V: C1.1, C2.1, C3.1, C4.1, C5.1, J6.2, J10.1, K2.1, R2.1, U1.1 (SwC), U1.6 (Vin), U1.8 (DC)
/Internal_Bat_Subsystem/INTBAT_12V: C9.1, D1.1 (K), D3.1 (K), D5.1 (K), K1.5, K3.5, K4.5, U2.3 (VO)
/Internal_Bat_Subsystem/INTBAT_GND: D1.2 (A), D3.2 (A), D5.2 (A), K1.2, K3.2, K4.2, Q3.2 (D), U6.2
/Internal_Bat_Subsystem/PWM_FAN: U4.3 (XTAL2/PB4), U6.1
/Internal_Bat_Subsystem/SCL: J6.4, J11.1, U4.7 (PB2)
/Internal_Bat_Subsystem/SDA: J6.5, J11.5, U4.5 (AREF/PB0)
/StepUp_15V/15V: C7.1, C8.1, D6.1 (K), D7.1 (K), J6.1
GND: BT2.2 (-), C1.2, C2.2, C3.2, C4.2, C5.2, C6.2, C7.2, C8.2, C9.2, C10.1, C11.2, C12.1, C13.2, D2.2 (A), J6.3, J9.1, J11.4, K2.2, PS1.2 (Vout+), Q2.3 (S), Q3.3 (S), R1.1, R3.2, R4.2, R5.1, R6.1, R7.2, U1.4 (GND), U2.2 (GND), U3.2 (GND), U4.4 (GND), U5.4 (GND), U6.4
unnamed: BT2.1 (+), D10.2 (A)
unnamed: D2.1 (K), K2.3, K2.5, PS1.1 (Vout-)
unnamed: D4.2 (A), Q1.1 (G), R1.2
unnamed: D4.1 (K), K4.1, Q1.3 (S)
unnamed: D6.2 (A), L1.2, Q2.2 (D)
unnamed: D7.2 (A), RV1.3
unnamed: D8.2 (A), J11.3, Q3.1 (G), R5.2, U4.6 (PB1)
unnamed: D8.1 (K), R6.2
unnamed: D9.2 (A), U4.2 (XTAL1/PB3)
unnamed: D9.1 (K), R7.1
unnamed: D10.1 (K), SW5.1 (A)
unnamed: J7.1, K1.3
unnamed: J8.1, K1.1, K3.1
unnamed: J8.2, PS1.3 (AC)
unnamed: J9.2, Q1.2 (D)
unnamed: J10.2, Q4.2 (D)
unnamed: J11.2, U4.1 (~RESET/PB5), U5.2 (IO)
unnamed: C11.1, C13.1, J11.6, U3.3 (OUT), U4.8 (VCC), U5.1 (VCC)
unnamed: K2.4, K4.3
unnamed: K3.3, PS1.4 (AC)
unnamed: Q2.1 (G), R3.1, U1.2 (SwE)
unnamed: Q4.1 (G), R8.1
unnamed: Q4.3 (S), R8.2, U6.5
unnamed: C10.2, C12.2, SW5.2 (B), U2.1 (VI), U3.1 (IN)
unnamed: L1.1, R2.2, U1.7 (Ipk)
unnamed: C6.1, U1.3 (TC)
unnamed: R4.1, RV1.1, RV1.2, U1.5 (Vfb)

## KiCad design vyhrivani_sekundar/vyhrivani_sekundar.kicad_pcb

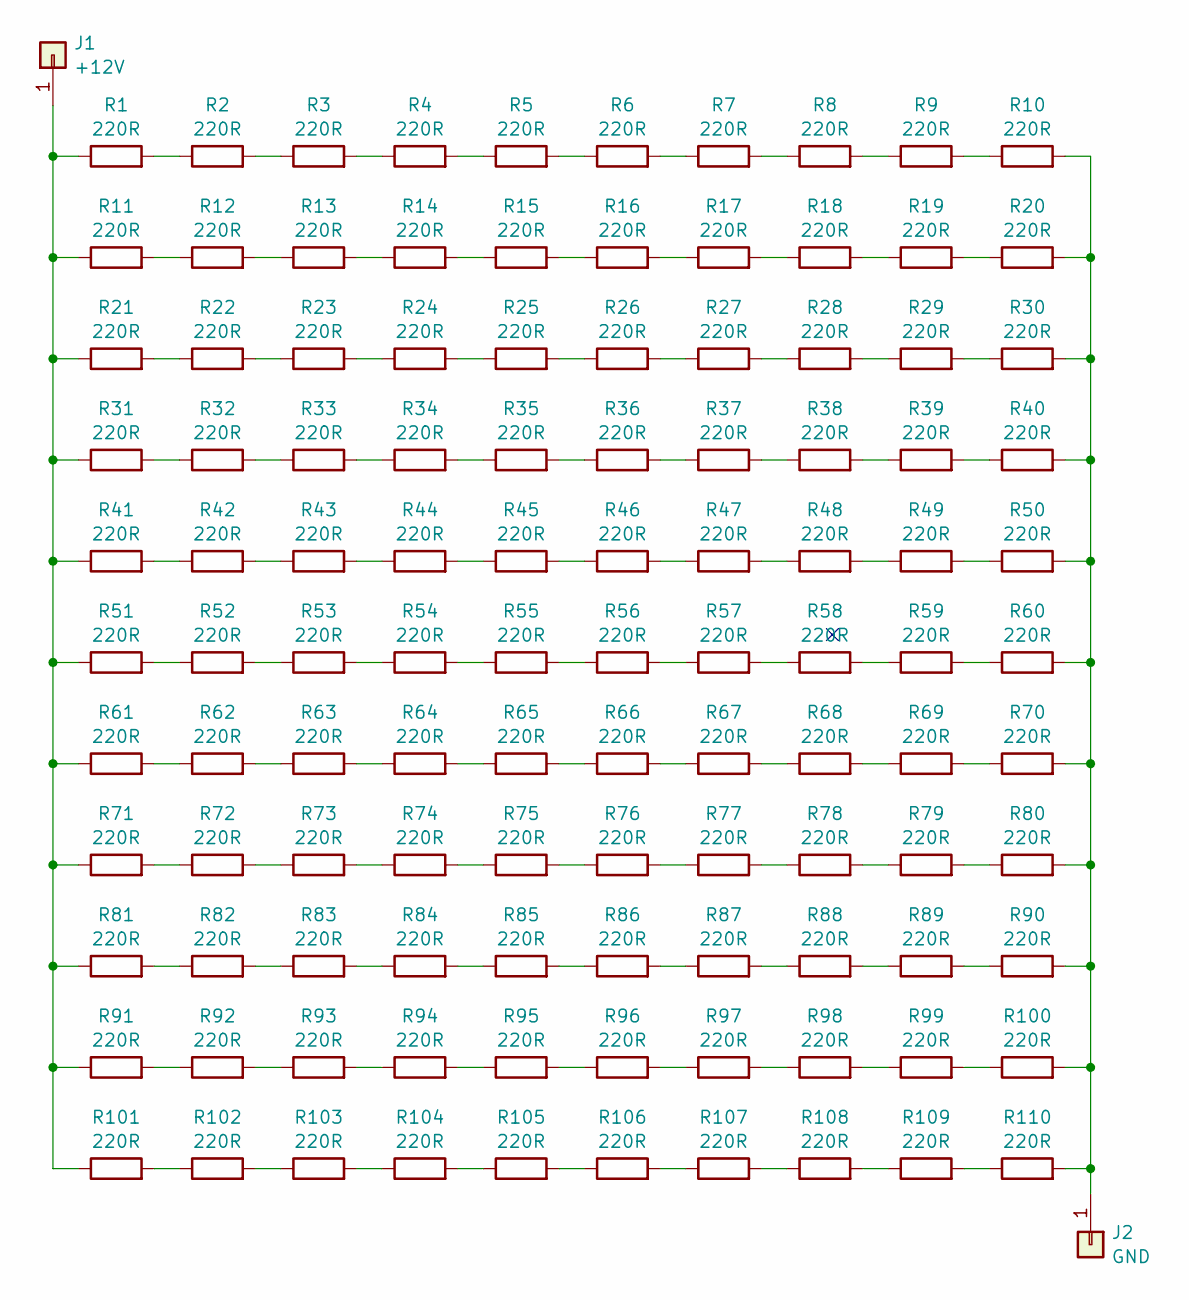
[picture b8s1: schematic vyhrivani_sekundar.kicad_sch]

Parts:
J1: +12V; SolderWirePad_1x01_SMD_1x2mm
J2: GND; SolderWirePad_1x01_SMD_1x2mm
R1, R2, R3, R4, R5, R6, R7, R8, R9, R10, R11, R12, R13, R14, R15, R16, R17, R18, R19, R20, R21, R22, R23, R24, R25, R26, R27, R28, R29, R30, R31, R32, R33, R34, R35, R36, R37, R38, R39, R40, R41, R42, R43, R44, R45, R46, R47, R48, R49, R50, R51, R52, R53, R54, R55, R56, R57, R58, R59, R60, R61, R62, R63, R64, R65, R66, R67, R68, R69, R70, R71, R72, R73, R74, R75, R76, R77, R78, R79, R80, R81, R82, R83, R84, R85, R86, R87, R88, R89, R90, R91, R92, R93, R94, R95, R96, R97, R98, R99, R100, R101, R102, R103, R104, R105, R106, R107, R108, R109, R110: 220R; R_0805_2012Metric_Pad1.20x1.40mm_HandSolder

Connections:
unnamed: J1.1, R1.1, R11.1, R21.1, R31.1, R41.1, R51.1, R61.1, R71.1, R81.1, R91.1, R101.1
unnamed: J2.1, R10.2, R20.2, R30.2, R40.2, R50.2, R60.2, R70.2, R80.2, R90.2, R100.2, R110.2
unnamed: R1.2, R2.1
unnamed: R2.2, R3.1
unnamed: R3.2, R4.1
unnamed: R4.2, R5.1
unnamed: R5.2, R6.1
unnamed: R6.2, R7.1
unnamed: R7.2, R8.1
unnamed: R8.2, R9.1
unnamed: R9.2, R10.1
unnamed: R11.2, R12.1
unnamed: R12.2, R13.1
unnamed: R13.2, R14.1
unnamed: R14.2, R15.1
unnamed: R15.2, R16.1
unnamed: R16.2, R17.1
unnamed: R17.2, R18.1
unnamed: R18.2, R19.1
unnamed: R19.2, R20.1
unnamed: R21.2, R22.1
unnamed: R22.2, R23.1
unnamed: R23.2, R24.1
unnamed: R24.2, R25.1
unnamed: R25.2, R26.1
unnamed: R26.2, R27.1
unnamed: R27.2, R28.1
unnamed: R28.2, R29.1
unnamed: R29.2, R30.1
unnamed: R31.2, R32.1
unnamed: R32.2, R33.1
unnamed: R33.2, R34.1
unnamed: R34.2, R35.1
unnamed: R35.2, R36.1
unnamed: R36.2, R37.1
unnamed: R37.2, R38.1
unnamed: R38.2, R39.1
unnamed: R39.2, R40.1
unnamed: R41.2, R42.1
unnamed: R42.2, R43.1
unnamed: R43.2, R44.1
unnamed: R44.2, R45.1
unnamed: R45.2, R46.1
unnamed: R46.2, R47.1
unnamed: R47.2, R48.1
unnamed: R48.2, R49.1
unnamed: R49.2, R50.1
unnamed: R51.2, R52.1
unnamed: R52.2, R53.1
unnamed: R53.2, R54.1
unnamed: R54.2, R55.1
unnamed: R55.2, R56.1
unnamed: R56.2, R57.1
unnamed: R57.2, R58.1
unnamed: R58.2, R59.1
unnamed: R59.2, R60.1
unnamed: R61.2, R62.1
unnamed: R62.2, R63.1
unnamed: R63.2, R64.1
unnamed: R64.2, R65.1
unnamed: R65.2, R66.1
unnamed: R66.2, R67.1
unnamed: R67.2, R68.1
unnamed: R68.2, R69.1
unnamed: R69.2, R70.1
unnamed: R71.2, R72.1
unnamed: R72.2, R73.1
unnamed: R73.2, R74.1
unnamed: R74.2, R75.1
unnamed: R75.2, R76.1
unnamed: R76.2, R77.1
unnamed: R77.2, R78.1
unnamed: R78.2, R79.1
unnamed: R79.2, R80.1
unnamed: R81.2, R82.1
unnamed: R82.2, R83.1
unnamed: R83.2, R84.1
unnamed: R84.2, R85.1
unnamed: R85.2, R86.1
unnamed: R86.2, R87.1
unnamed: R87.2, R88.1
unnamed: R88.2, R89.1
unnamed: R89.2, R90.1
unnamed: R91.2, R92.1
unnamed: R92.2, R93.1
unnamed: R93.2, R94.1
unnamed: R94.2, R95.1
unnamed: R95.2, R96.1
unnamed: R96.2, R97.1
unnamed: R97.2, R98.1
unnamed: R98.2, R99.1
unnamed: R99.2, R100.1
unnamed: R101.2, R102.1
unnamed: R102.2, R103.1
unnamed: R103.2, R104.1
unnamed: R104.2, R105.1
unnamed: R105.2, R106.1
unnamed: R106.2, R107.1
unnamed: R107.2, R108.1
unnamed: R108.2, R109.1
unnamed: R109.2, R110.1

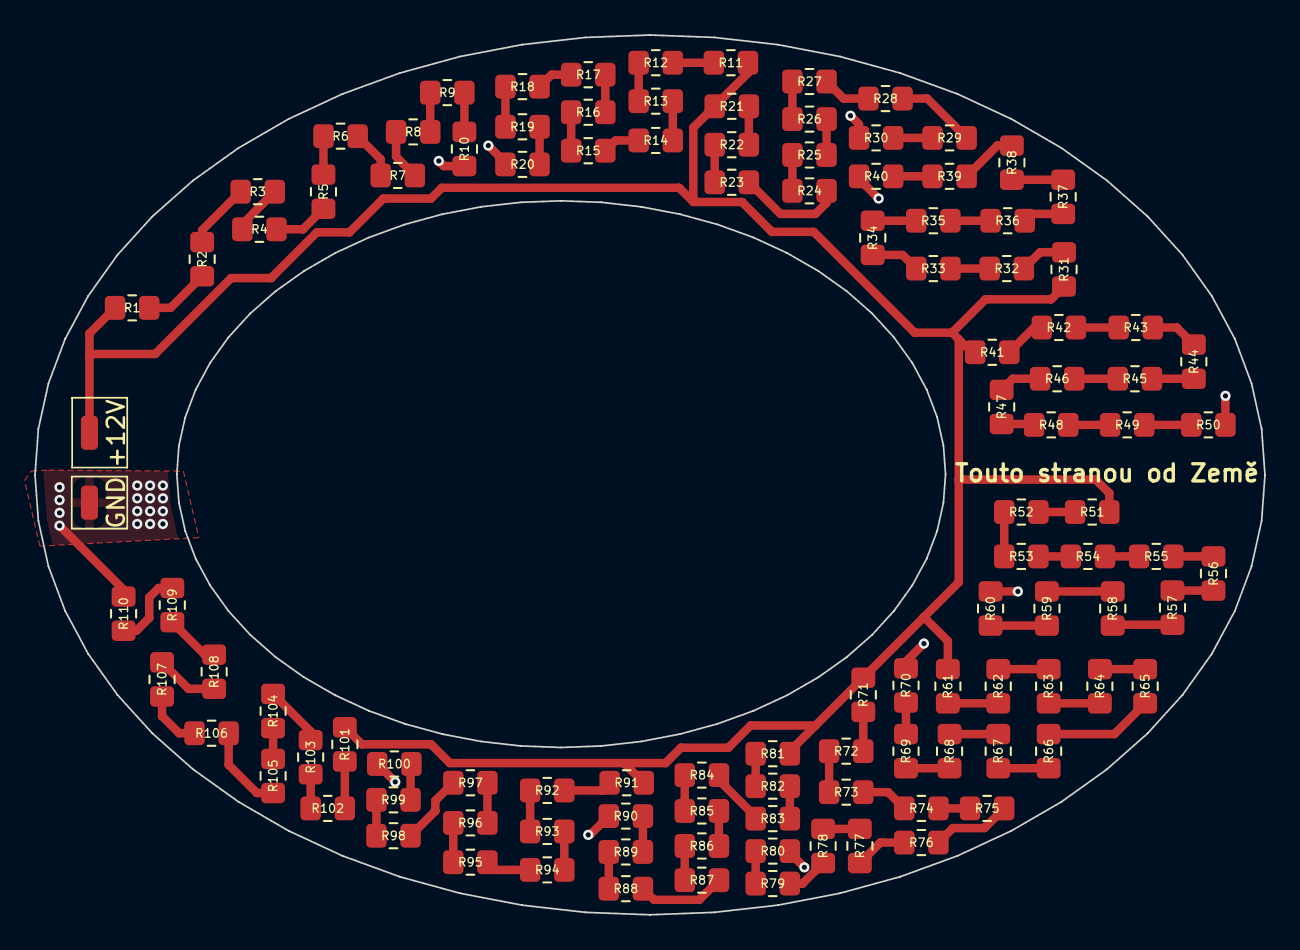
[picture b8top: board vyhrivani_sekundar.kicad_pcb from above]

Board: 2 copper layers, 72.0 x 51.5 mm, 112 parts (0 on the bottom side), 101 nets.

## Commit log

2024-05-01 KiCAD projects cleaning
2025-05-12 .gitignore
2025-05-12 Vyhrivaci deska sekundaru
2025-05-12 astrobox WIP
2025-05-12 sekundar render
2025-10-29 WIP medium astrobox
2025-11-14 medium astrobox in multiple boards
2025-11-14 WIP control board
2025-11-21 astrobox medium final pcb
2025-11-21 init software for PWM control
2025-11-21 libs out
2025-11-25 Init software for medium box
2026-04-24 Control board update
2026-04-24 Lista k radioteleskopu
2026-04-24 WIP: Frezovany pavouk + krabice na radio controller
2026-04-24 Radiobox spodek + STEP
